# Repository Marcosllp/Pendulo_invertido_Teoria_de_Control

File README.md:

# Bibliografía

- [Microcontrolador ESP32-devKitC V4](https://docs.espressif.com/projects/esp-idf/en/latest/esp32/hw-reference/esp32/get-started-devkitc.html)

- [Giroscopio MPU6050](https://naylampmechatronics.com/blog/45_tutorial-mpu6050-acelerometro-y-giroscopio.html)

- [Driver TB6612FNG](https://www.luisllamas.es/arduino-motor-dc-tb6612fng)

- [Regulador AMS117 5V](https://datasheet.octopart.com/AMS1117-5.0-ams-datasheet-34441097.pdf?_gl=1*9dnc4b*_ga*NzUwMjQyMDcyLjE3MTA4NTgxMTI.*_ga_SNYD338KXX*MTcxMDg1ODExMi4xLjEuMTcxMDg1ODEzMy4wLjAuMA..)

- [Condensador para el regulador (220uF 16v)](https://c1555f5ec9.clvaw-cdnwnd.com/34662fcf1f1e607c561442431023ac8e/200000360-636e0646b8/Cap%20Electrolitic%2010-100V%20-%200.1%20to%2022000uF%20Datasheet.pdf)

# Diseño PCB

- ## PCB schematics

- ## PCB footprint

- ## PCB 3D

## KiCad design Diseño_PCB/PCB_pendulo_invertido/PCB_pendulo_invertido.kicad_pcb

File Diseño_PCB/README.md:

# Diseño PCB
## PCB schematics

## PCB blueprint

## PCB 3D

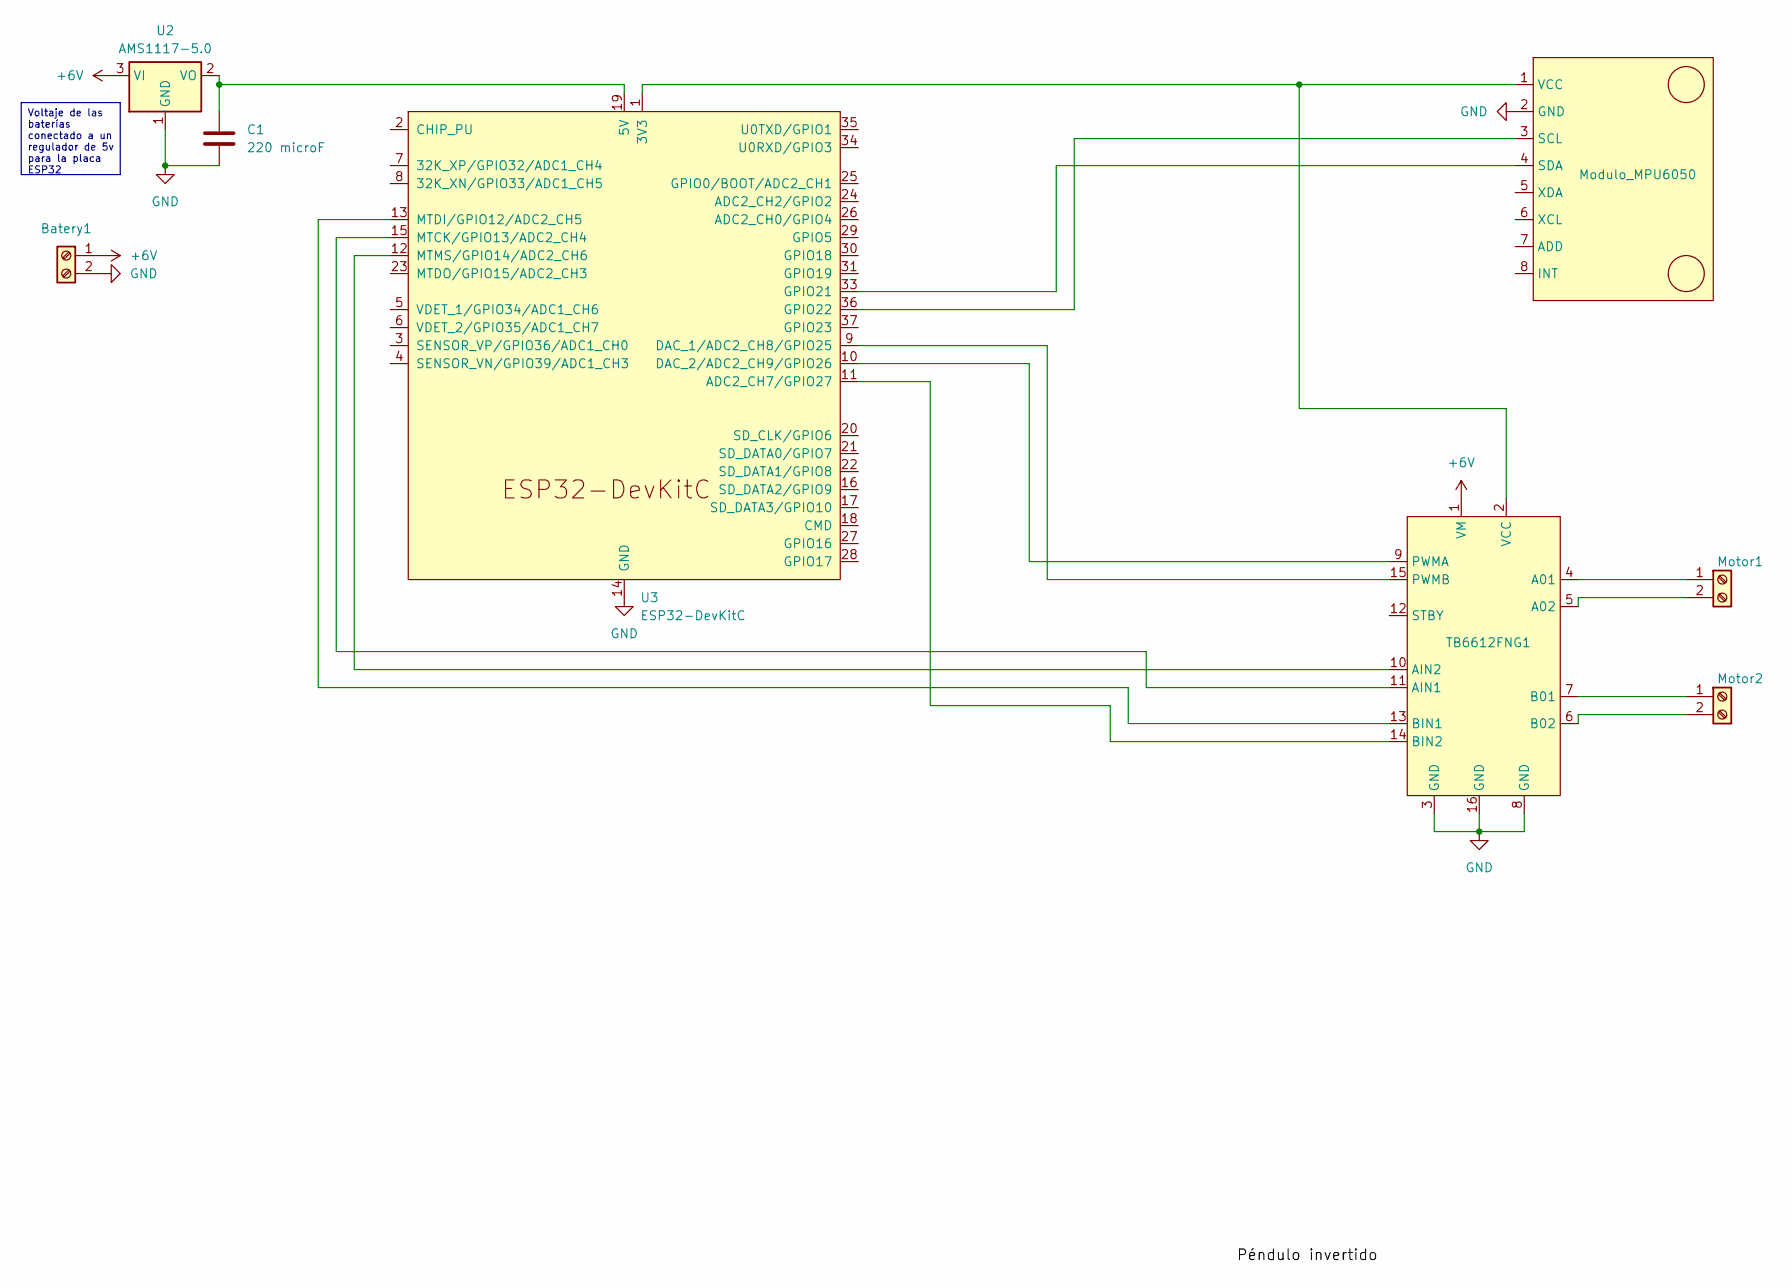
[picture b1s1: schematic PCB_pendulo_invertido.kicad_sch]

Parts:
Batery1: Screw_Terminal_01x02; TerminalBlock_bornier-2_P5.08mm
C1: 220 microF; CP_Radial_D6.3mm_P2.50mm
Modulo_MPU6050: mpu6050 prueba
Motor1, Motor2: Screw_Terminal_01x02; TerminalBlock_bornier-2_P5.08mm
TB6612FNG1: Módulo TB6612FNG
U2: AMS1117-5.0; SOT-223-3_TabPin2
U3: ESP32-DevKitC

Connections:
+6V: Batery1.1, TB6612FNG1.1 (VM), U2.3 (VI)
GND: Batery1.2, C1.2, Modulo_MPU6050.2 (GND), TB6612FNG1.3 (GND), TB6612FNG1.8 (GND), TB6612FNG1.16 (GND), U2.1 (GND), U3.14 (GND), U3.32 (GND), U3.38 (GND)
unnamed: Modulo_MPU6050.3 (SCL), U3.36 (GPIO22)
unnamed: Modulo_MPU6050.4 (SDA), U3.33 (GPIO21)
unnamed: Modulo_MPU6050.1 (VCC), TB6612FNG1.2 (VCC), U3.1 (3V3)
unnamed: Motor1.1, TB6612FNG1.4 (A01)
unnamed: Motor1.2, TB6612FNG1.5 (A02)
unnamed: Motor2.1, TB6612FNG1.7 (B01)
unnamed: Motor2.2, TB6612FNG1.6 (B02)
unnamed: TB6612FNG1.11 (AIN1), U3.15 (MTCK/GPIO13/ADC2_CH4)
unnamed: TB6612FNG1.10 (AIN2), U3.12 (MTMS/GPIO14/ADC2_CH6)
unnamed: TB6612FNG1.13 (BIN1), U3.13 (MTDI/GPIO12/ADC2_CH5)
unnamed: TB6612FNG1.14 (BIN2), U3.11 (ADC2_CH7/GPIO27)
unnamed: TB6612FNG1.9 (PWMA), U3.10 (DAC_2/ADC2_CH9/GPIO26)
unnamed: TB6612FNG1.15 (PWMB), U3.9 (DAC_1/ADC2_CH8/GPIO25)
unnamed: C1.1, U2.2 (VO), U3.19 (5V)

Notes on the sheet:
Voltaje de las baterías conectado a un regulador de 5v para la placa ESP32

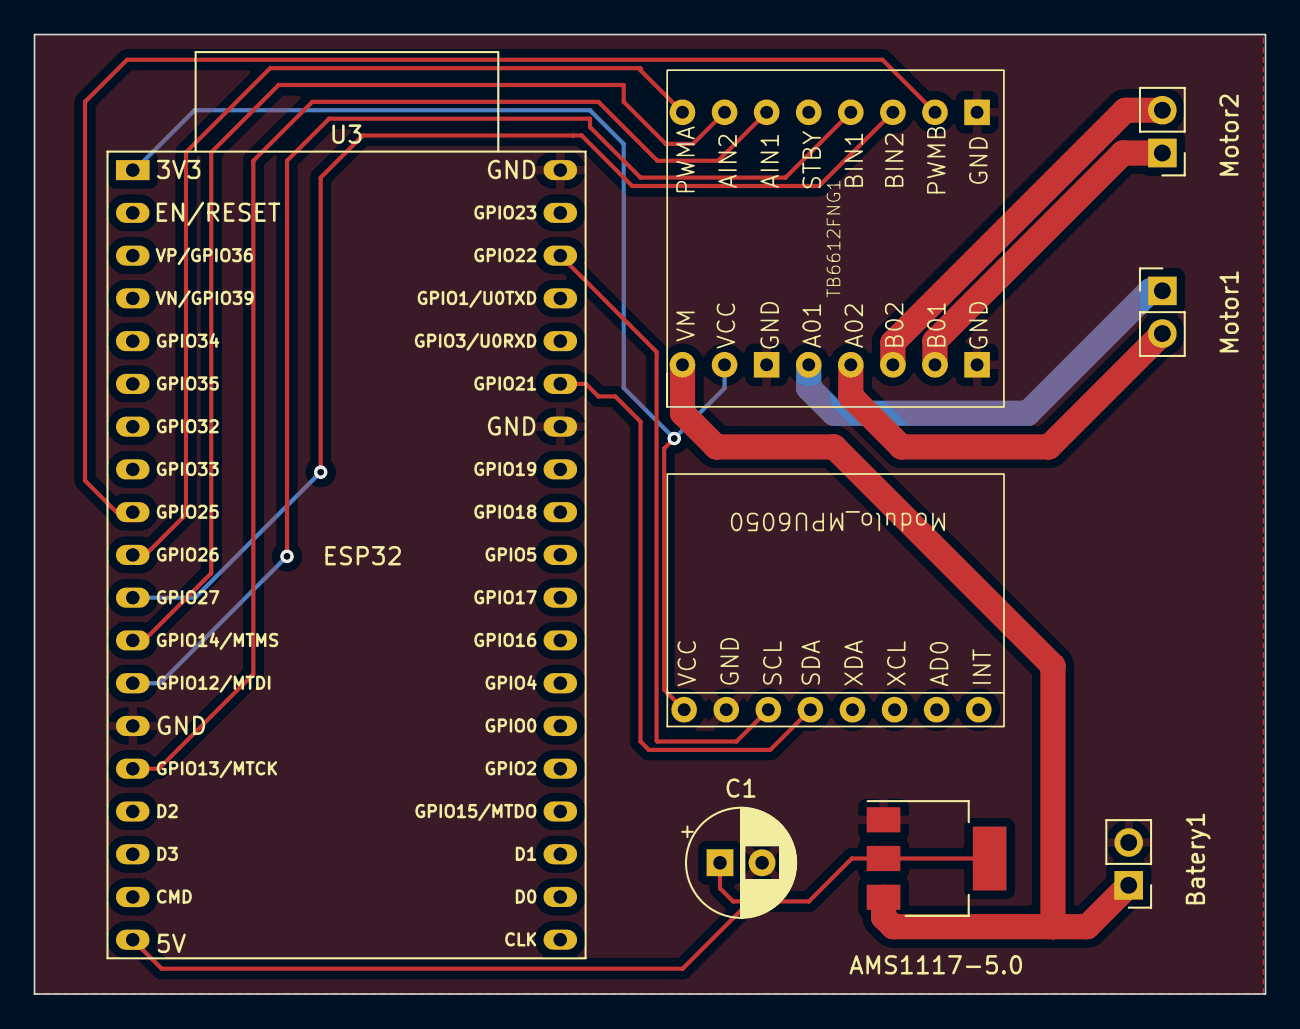
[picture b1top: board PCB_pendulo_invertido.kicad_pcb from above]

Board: 2 copper layers, 73.1 x 57.0 mm, 8 parts (0 on the bottom side), 16 nets.

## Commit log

2024-02-29 Update README.md
    Bibliografías de los principales componentes del proyecto
2024-02-29 Create README.md
    Bibliografía de los principales componentes del proyecto
2024-02-29 Update README.md
    Bibliografía de los principales componentes del proyecto
2024-03-20 Subida de la carpeta de kikad del diseño de la PCB
2024-03-20 Esquemático del circuito
2024-03-20 Plano de la pcb
2024-07-21 Subida de librería practica 4 Teoría de Control
2024-07-21 Base pendulo invertido
    Subida de la plataforma base donde va montada encima la PCB, impresa en impresora 3d
